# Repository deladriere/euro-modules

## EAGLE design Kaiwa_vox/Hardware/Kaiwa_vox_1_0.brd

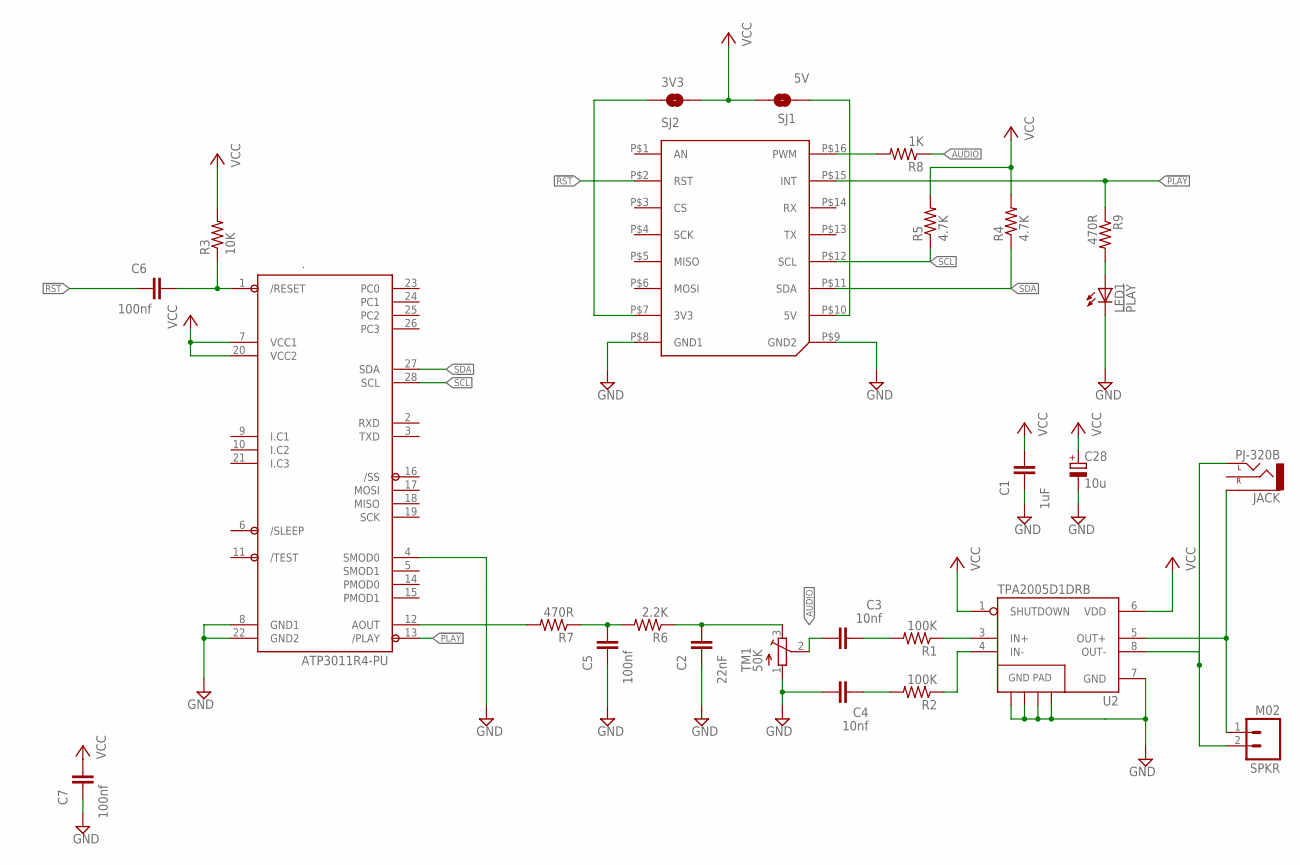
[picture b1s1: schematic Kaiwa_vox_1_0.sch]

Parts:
.: ATP3011R4-PU; DIP28
C1: 1uF; SPARKFUN_0805
C2: 22nF; SPARKFUN_0805
C3, C4: 10nf; SPARKFUN_0805
C5, C6, C7: 100nf; SPARKFUN_0805
C28: 10u; A/3216-18R
CLICK: MIKROE_CLICKLARGE; MIKROE_BUS_LARGE
JACK: PJ-320B; FOOTPRINT
LED1: !PLAY; SML0603
R1, R2: 100K; SPARKFUN_0805
R3: 10K; SPARKFUN_0805
R4, R5: 4.7K; SPARKFUN_0805
R6: 2.2K; SPARKFUN_0805
R7, R9: 470R; SPARKFUN_0805
R8: 1K; SPARKFUN_0805
SJ1: 5V; SPARKFUN_SJ_2S-TRACE
SJ2: 3V3; SPARKFUN_SJ_2S-NO
SPKR: M02; 1X02_LOCK_LONGPADS
TM1: 50K; TC33X
U2: TPA2005D1DRB; QFN-8_PAD

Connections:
!PLAY: ..13 (/PLAY), CLICK.P$15 (INT), R9.1
!RST: C6.2, CLICK.P$2 (RST)
AUDIO: C3.1, R8.1, TM1.2 (S)
GND: ..4 (SMOD0), ..8 (GND1), ..22 (GND2), C1.2, C2.2, C4.1, C5.2, C7.2, C28.-, CLICK.P$8 (GND1), CLICK.P$9 (GND2), LED1.C, TM1.1 (A), U2.7 (GND), U2.10 (GND), U2.11 (GND), U2.12 (GND), U2.13 (GND)
unnamed: ..1 (/RESET), C6.1, R3.1
unnamed: JACK.4 (SLEEVE), SPKR.1, U2.5 (OUT+)
unnamed: CLICK.P$7 (3V3), SJ2.1
unnamed: CLICK.P$10 (5V), SJ1.1
unnamed: C5.1, R6.2, R7.1
unnamed: C2.1, R6.1, TM1.3 (E)
unnamed: JACK.2 (LEFT), SPKR.2, U2.8 (OUT-)
unnamed: R1.1, U2.3 (IN+)
unnamed: R2.1, U2.4 (IN-)
unnamed: C4.2, R2.2
unnamed: CLICK.P$16 (PWM), R8.2
unnamed: C3.2, R1.2
unnamed: LED1.A, R9.2
unnamed: ..12 (AOUT), R7.2
SCL: ..28 (SCL), CLICK.P$12 (SCL), R5.1
SDA: ..27 (SDA), CLICK.P$11 (SDA), R4.1
VCC: ..7 (VCC1), ..20 (VCC2), C1.1, C7.1, C28.+, R3.2, R4.2, R5.2, SJ1.2, SJ2.2, U2.1 (SHUTDOWN), U2.6 (VDD)

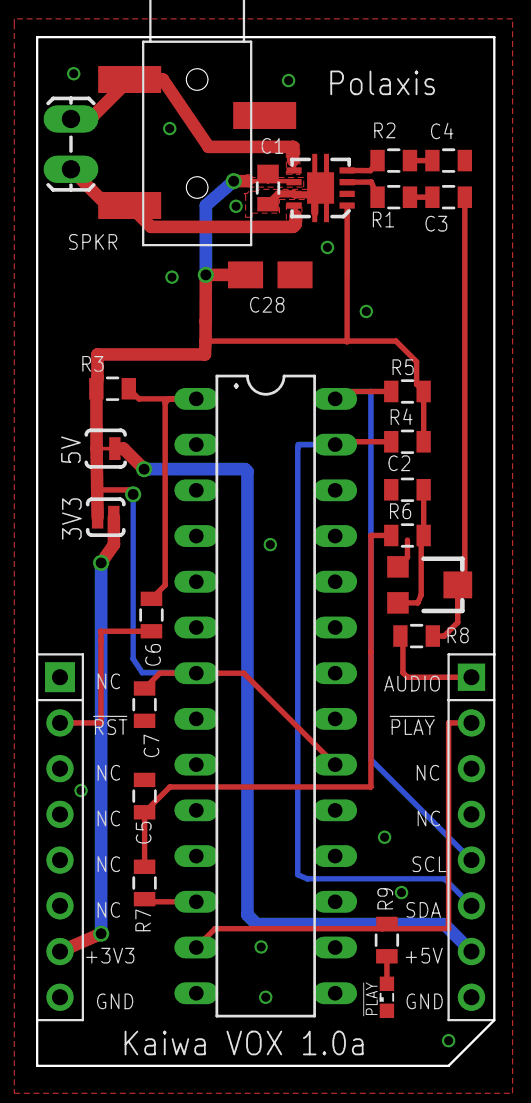
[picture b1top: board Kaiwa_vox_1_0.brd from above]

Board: 2 copper layers, 25.4 x 57.1 mm, 26 parts (0 on the bottom side), 21 nets.

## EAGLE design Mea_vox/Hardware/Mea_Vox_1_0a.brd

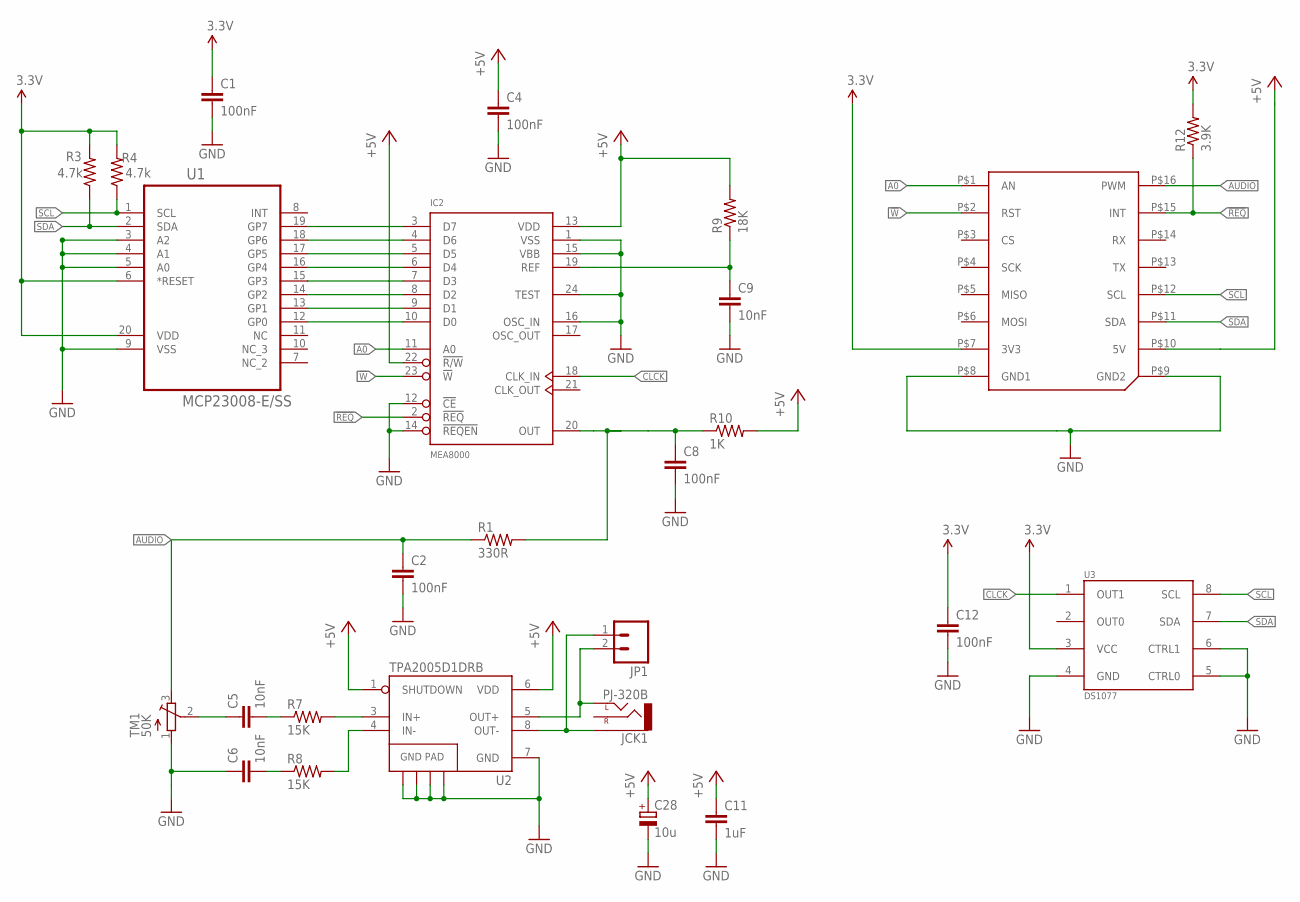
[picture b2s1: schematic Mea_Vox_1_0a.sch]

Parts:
C1, C2, C4, C8, C12: 100nF; SPARKFUN_0805
C5, C6, C9: 10nF; SPARKFUN_0805
C11: 1uF; SPARKFUN_0805
C28: 10u; A/3216-18R
IC2: MEA8000; DIL24-6
JCK1: PJ-320B; FOOTPRINT
JP1: M02PTH; 1X02
MK1: MIKROE_CLICKLARGE; MIKROE_BUS_LARGE
R1: 330R; SPARKFUN_0805
R3, R4: 4.7k; SPARKFUN_0805
R7, R8: 15K; SPARKFUN_0805
R9: 18K; SPARKFUN_0805
R10: 1K; SPARKFUN_0805
R12: 3.9K; SPARKFUN_0805
TM1: 50K; TC33X
U1: MCP23008-E/SS; SOP65P780X200-20N
U2: TPA2005D1DRB; QFN-8_PAD
U3: DS1077; SO08

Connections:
3.3V: C1.1, C12.1, MK1.P$7 (3V3), R3.2, R4.2, R12.2, U1.6 (*RESET), U1.20 (VDD), U3.3 (VCC)
!REQ: IC2.2 (!REQ), MK1.P$15 (INT), R12.1
!W: IC2.23 (!W), MK1.P$2 (RST)
+5V: C4.1, C11.1, C28.+, IC2.13 (VDD), IC2.22 (!R/W), MK1.P$10 (5V), R9.2, R10.2, U2.1 (SHUTDOWN), U2.6 (VDD)
A0: IC2.11 (A0), MK1.P$1 (AN)
AUDIO: C2.1, MK1.P$16 (PWM), R1.1, TM1.3 (E)
CLCK: IC2.18 (CLK_IN), U3.1 (OUT1)
GND: C1.2, C2.2, C4.2, C6.1, C8.2, C9.2, C11.2, C12.2, C28.-, IC2.1 (VSS), IC2.12 (!CE), IC2.14 (!REQEN), IC2.15 (VBB), IC2.16 (OSC_IN), IC2.24 (TEST), MK1.P$8 (GND1), MK1.P$9 (GND2), TM1.1 (A), U1.3 (A2), U1.4 (A1), U1.5 (A0), U1.9 (VSS), U2.7 (GND), U2.10 (GND), U2.11 (GND), U2.12 (GND), U2.13 (GND), U3.4 (GND), U3.5 (CTRL0), U3.6 (CTRL1)
unnamed: JCK1.4 (SLEEVE), JP1.1, U2.8 (OUT-)
unnamed: IC2.10 (D0), U1.12 (GP0)
unnamed: IC2.9 (D1), U1.13 (GP1)
unnamed: IC2.8 (D2), U1.14 (GP2)
unnamed: IC2.7 (D3), U1.15 (GP3)
unnamed: IC2.6 (D4), U1.16 (GP4)
unnamed: IC2.5 (D5), U1.17 (GP5)
unnamed: IC2.4 (D6), U1.18 (GP6)
unnamed: IC2.3 (D7), U1.19 (GP7)
unnamed: JCK1.2 (LEFT), JP1.2, U2.5 (OUT+)
unnamed: R7.2, U2.3 (IN+)
unnamed: R8.2, U2.4 (IN-)
unnamed: C6.2, R8.1
unnamed: C5.2, R7.1
unnamed: C8.1, IC2.20 (OUT), R1.2, R10.1
unnamed: C5.1, TM1.2 (S)
unnamed: C9.1, IC2.19 (REF), R9.1
SCL: MK1.P$12 (SCL), R4.1, U1.1 (SCL), U3.8 (SCL)
SDA: MK1.P$11 (SDA), R3.1, U1.2 (SDA), U3.7 (SDA)

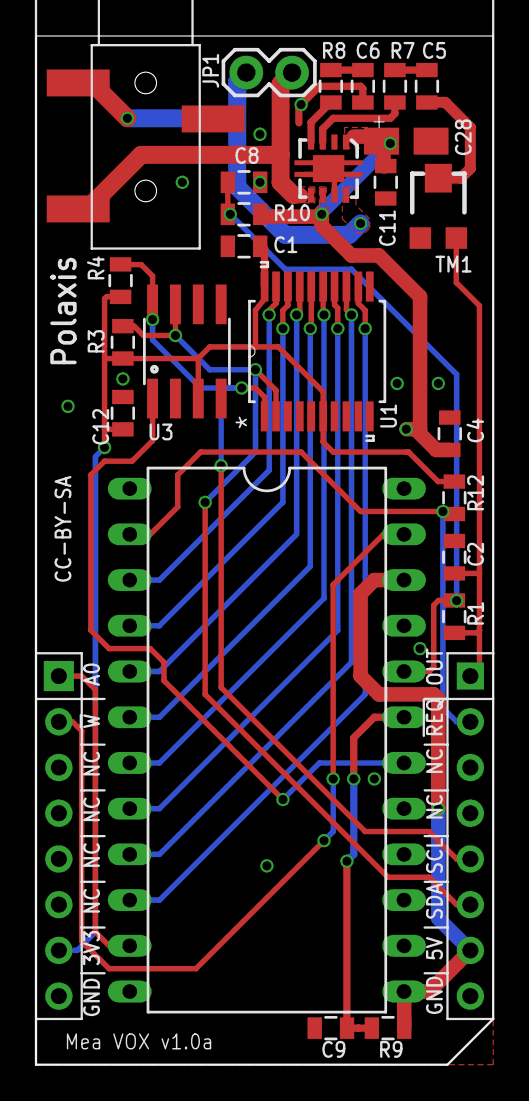
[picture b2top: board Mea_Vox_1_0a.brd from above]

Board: 2 copper layers, 25.4 x 57.1 mm, 26 parts (0 on the bottom side), 27 nets.

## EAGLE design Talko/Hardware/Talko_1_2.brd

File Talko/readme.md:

### Hardware revisions

Talko 1.0 (October 2014)
- initial release

Talko 1.1 (June 2015)
- higher resistors values for the LED (too bright) 
- removed the RC filter : I prefer the metallic sound it produces without the RC audio filter 
- swap Pitch & Speed pots as suggested
- fixed the LED ground connection missing

Talko 1.2 (May 2016)
- fixed a missing via
 - Audio output protected against mistake of over or under voltage by clipping from 0 to +5V 
- Rotary encoder for instant Bank change via interrupts
- Encoder's button to simulate gate signal going HIGH and make the module speak when pressed 
- Mode selection now a 3 positions switch 
- Break out 4 ATmega328p free pins for hacking (included A4 A5 for I2C bus) 
- Proper orientation of potentiomers

### Software revisions

Please note that hardware version need specific firmware version. They are not cross-compatible 

More info here : http://www.polaxis.be/talko/  
License: CC-BY-SA

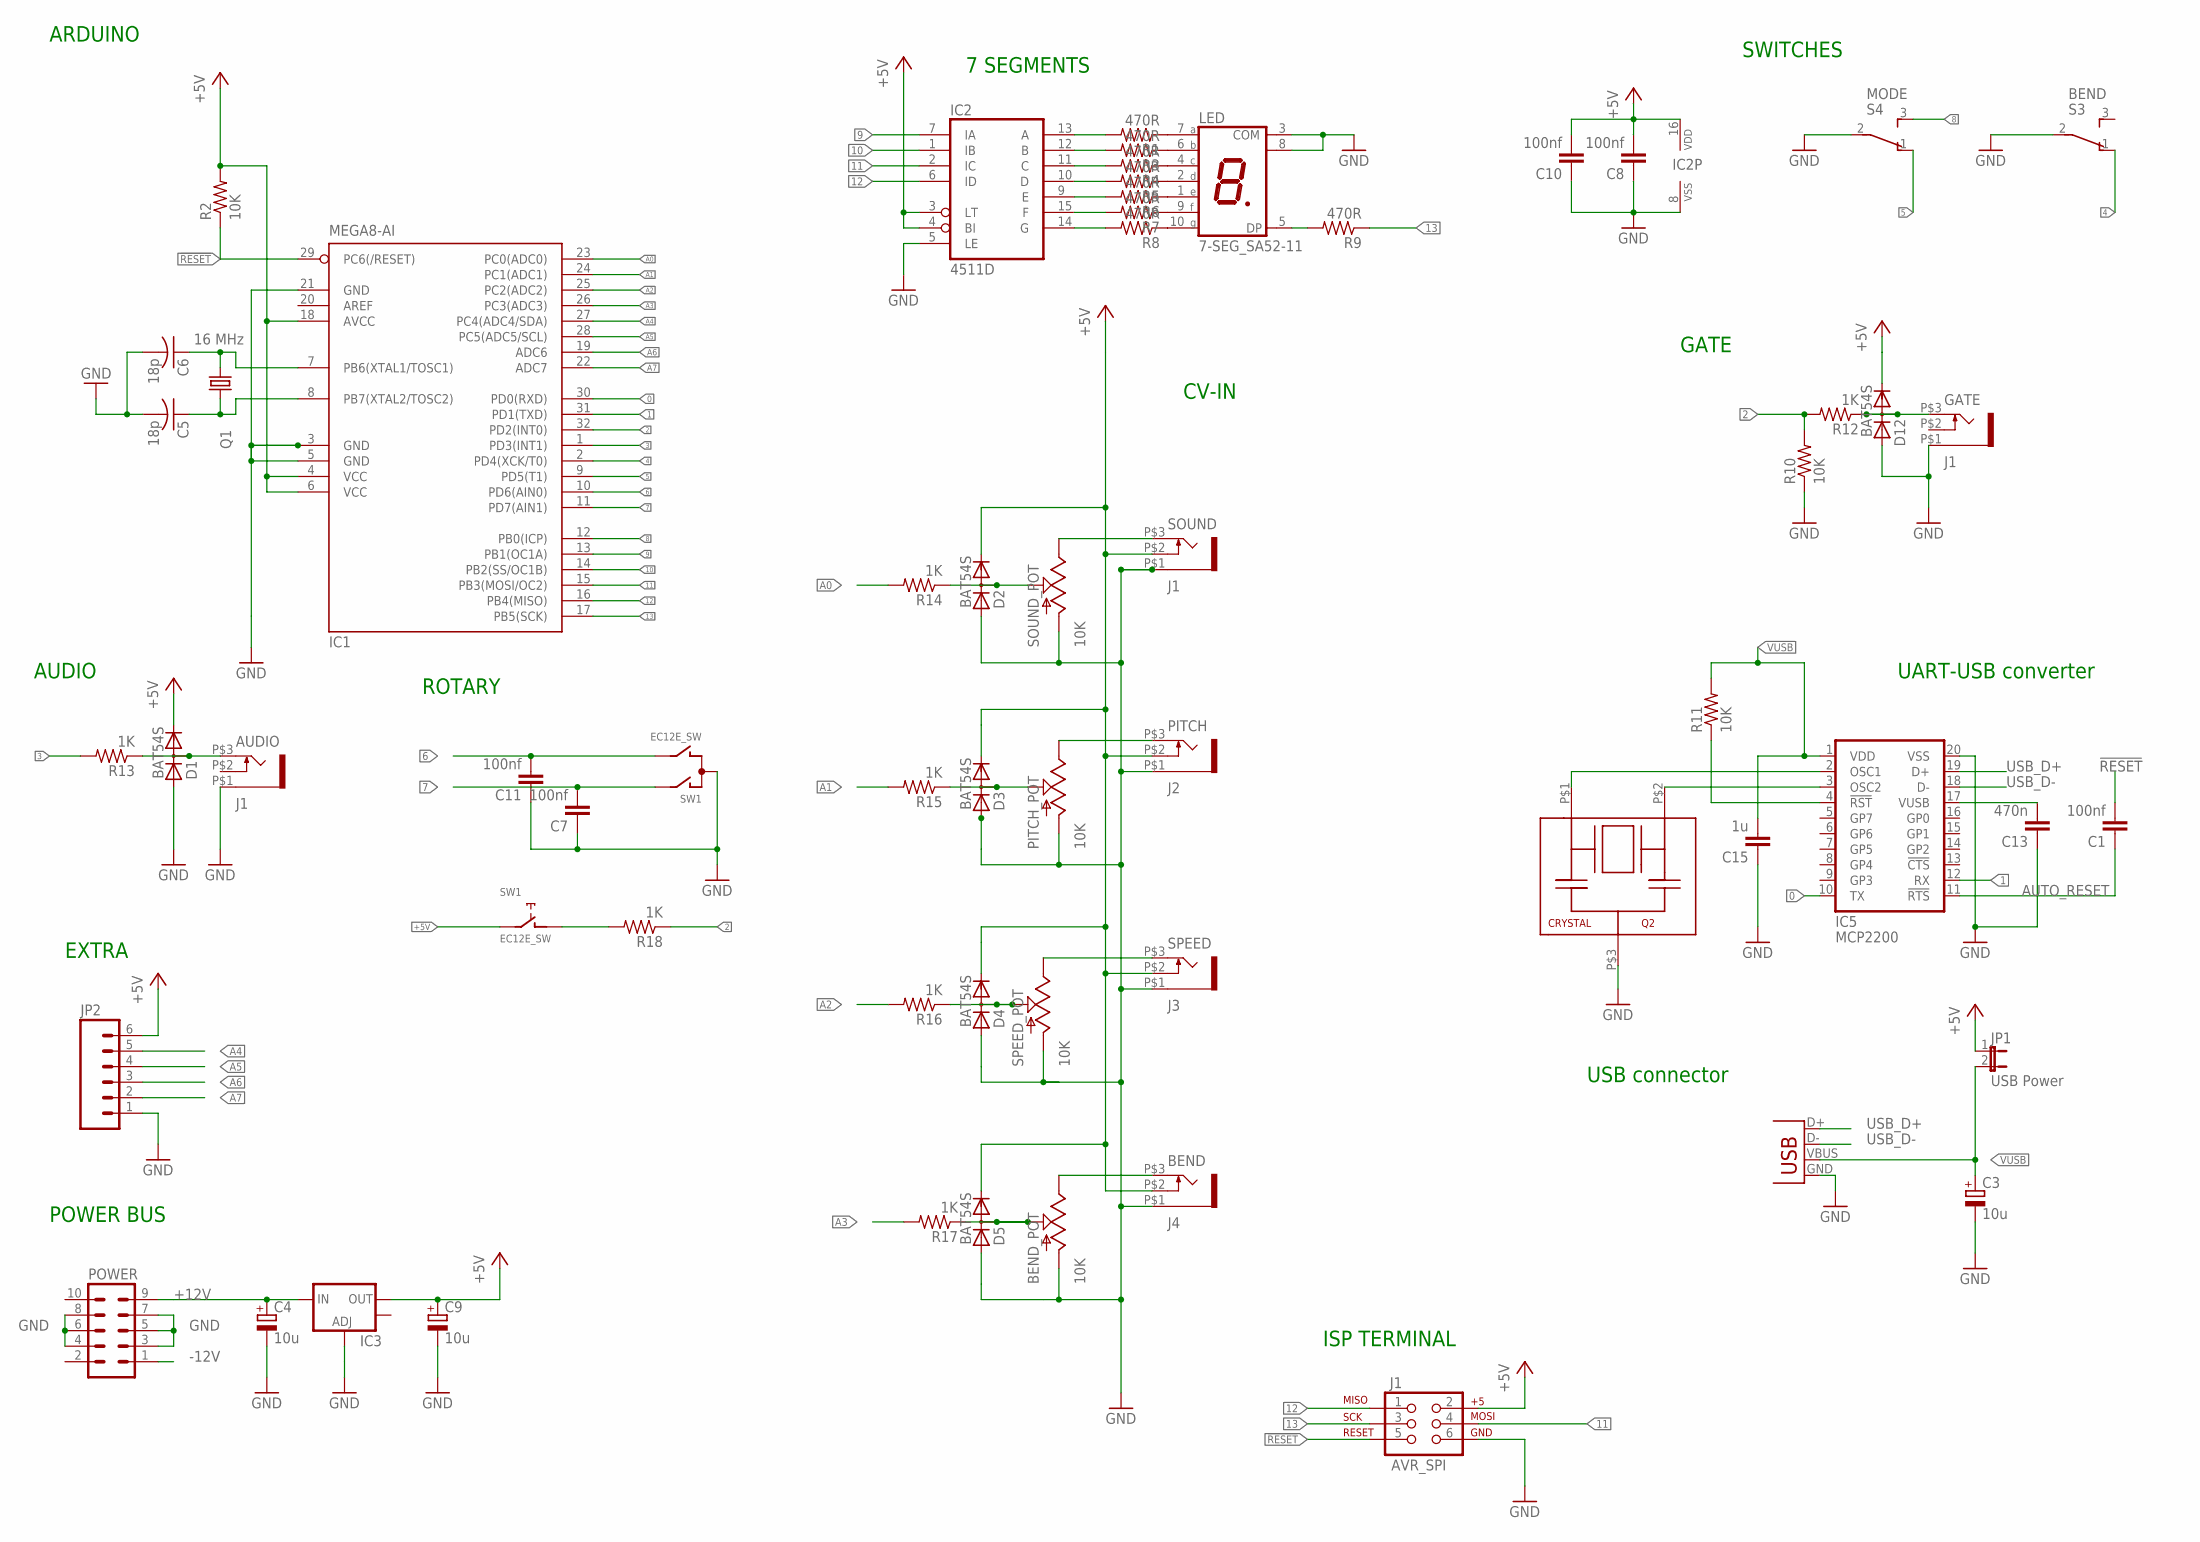
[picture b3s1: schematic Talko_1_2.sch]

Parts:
AUDIO: J1; THONKICONN
BEND: J4; THONKICONN
BEND_POT: 10K; ALPS_POT
C1, C7, C8, C10, C11: 100nf; C0805
C3, C4, C9: 10u; R/2012-12R
C5, C6: 18p; C0805K
C13: 470n; 0805
C15: 1u; 0805
D1, D2, D3, D4, D5, D12: BAT54S; SOT23
GATE: J1; THONKICONN
IC1: MEGA8-AI; TQFP32-08
IC2: 4511D; SO16
IC3: V_REG_LM1117SOT223; SOT223
IC5: MCP2200; SO20
J1: AVR_SPI; 2X3_LOCK
JP1: USB Power; JP1
JP2: M06SIP; 1X06
LED: 7-SEG_SA52-11; SA52-11
PITCH: J2; THONKICONN
PITCH_POT: 10K; ALPS_POT
POWER: 10_PIN_HEADER; MA05-2
Q1: 16 MHz; CTS406
Q2: CRYSTAL
R1, R3, R4, R5, R6, R7, R8, R9: 470R; M0805
R2, R10, R11: 10K; M0805
R12, R13, R14, R15, R16, R17, R18: 1K; M0805
S3: BEND; TL3XPO
S4: MODE; TL3XPO
SOUND: J1; THONKICONN
SOUND_POT: 10K; ALPS_POT
SPEED: J3; THONKICONN
SPEED_POT: 10K; ALPS_POT
SW1: EC12E_SW; ALPS_EC12E_SW
X3: USB; USB-B-PTH-VERTICAL

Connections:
0: IC1.30 (PD0(RXD)), IC5.10 (TX)
1: IC1.31 (PD1(TXD)), IC5.12 (RX)
2: IC1.32 (PD2(INT0)), R10.2, R12.2, R18.1
3: IC1.1 (PD3(INT1)), R13.2
4: IC1.2 (PD4(XCK/T0)), S3.1 (O)
5: IC1.9 (PD5(T1)), S4.1 (O)
6: C11.2, IC1.10 (PD6(AIN0)), SW1.B
7: C7.2, IC1.11 (PD7(AIN1)), SW1.A
8: IC1.12 (PB0(ICP)), S4.3 (S)
9: IC1.13 (PB1(OC1A)), IC2.7 (IA)
10: IC1.14 (PB2(SS/OC1B)), IC2.1 (IB)
11: IC1.15 (PB3(MOSI/OC2)), IC2.2 (IC), J1.4
12: IC1.16 (PB4(MISO)), IC2.6 (ID), J1.1
13: IC1.17 (PB5(SCK)), J1.3, R9.1
!RESET: C1.2, IC1.29 (PC6(/RESET)), J1.5, R2.1
+5V: BEND.P$2 (4), C8.2, C9.+, C10.2, D1.2 (C), D2.2 (C), D3.2 (C), D4.2 (C), D5.2 (C), D12.2 (C), IC1.4 (VCC), IC1.6 (VCC), IC1.18 (AVCC), IC2.3 (LT), IC2.4 (BI), IC2.16 (VDD), IC3.2 (OUT), J1.2, JP1.1, JP2.6, PITCH.P$2 (4), R2.2, SOUND.P$2 (4), SPEED.P$2 (4), SW1.E (2)
+12V: C4.+, IC3.3 (IN), POWER.9
-12V: POWER.1
A0: IC1.23 (PC0(ADC0)), R14.2
A1: IC1.24 (PC1(ADC1)), R15.2
A2: IC1.25 (PC2(ADC2)), R16.2
A3: IC1.26 (PC3(ADC3)), R17.2
A4: IC1.27 (PC4(ADC4/SDA)), JP2.5
A5: IC1.28 (PC5(ADC5/SCL)), JP2.4
A6: IC1.19 (ADC6), JP2.3
A7: IC1.22 (ADC7), JP2.2
AUTO_RESET: C1.1, IC5.11 (!RTS)
GND: AUDIO.P$1 (5), BEND.P$1 (5), BEND_POT.P$3 (A), C3.-, C4.-, C5.2, C6.2, C7.1, C8.1, C9.-, C10.1, C11.1, C13.1, C15.1, D1.1 (A), D2.1 (A), D3.1 (A), D4.1 (A), D5.1 (A), D12.1 (A), GATE.P$1 (5), IC1.3 (GND), IC1.5 (GND), IC1.21 (GND), IC2.5 (LE), IC2.8 (VSS), IC3.1 (ADJ), IC5.20 (VSS), J1.6, JP2.1, LED.3 (COM), LED.8 (COM), PITCH.P$1 (5), PITCH_POT.P$3 (A), POWER.3, POWER.4, POWER.5, POWER.6, POWER.7, POWER.8, Q2.P$3 (3), R10.1, S3.2, S4.2, SOUND.P$1 (5), SOUND_POT.P$3 (A), SPEED.P$1 (5), SPEED_POT.P$3 (A), SW1.C, X3.GND
unnamed: D12.3 (AC), GATE.P$3 (3), R12.1
unnamed: SOUND.P$3 (3), SOUND_POT.P$1 (E)
unnamed: C5.1, IC1.8 (PB7(XTAL2/TOSC2)), Q1.1
unnamed: LED.5 (DP), R9.2
unnamed: PITCH.P$3 (3), PITCH_POT.P$1 (E)
unnamed: AUDIO.P$3 (3), D1.3 (AC), R13.1
unnamed: SPEED.P$3 (3), SPEED_POT.P$1 (E)
unnamed: IC2.13 (A), R1.2
unnamed: D2.3 (AC), R14.1, SOUND_POT.P$2 (S)
unnamed: LED.7 (A), R1.1
unnamed: IC5.3 (OSC2), Q2.P$2 (2)
unnamed: C6.1, IC1.7 (PB6(XTAL1/TOSC1)), Q1.3 (2)
unnamed: R18.2, SW1.D (1)
unnamed: IC2.12 (B), R3.2
unnamed: LED.6 (B), R3.1
unnamed: IC2.11 (C), R4.2
unnamed: LED.4 (C), R4.1
unnamed: IC2.10 (D), R5.2
unnamed: LED.2 (D), R5.1
unnamed: IC2.9 (E), R6.2
unnamed: LED.1 (E), R6.1
unnamed: IC2.15 (F), R7.2
unnamed: LED.9 (F), R7.1
unnamed: IC2.14 (G), R8.2
unnamed: LED.10 (G), R8.1
unnamed: IC5.2 (OSC1), Q2.P$1 (1)
unnamed: IC5.4 (!RST), R11.1
unnamed: C13.2, IC5.17 (VUSB)
unnamed: D4.3 (AC), R16.1, SPEED_POT.P$2 (S)
unnamed: D3.3 (AC), PITCH_POT.P$2 (S), R15.1
unnamed: BEND_POT.P$2 (S), D5.3 (AC), R17.1
unnamed: BEND.P$3 (3), BEND_POT.P$1 (E)
USB_D+: IC5.19 (D+), X3.D+
USB_D-: IC5.18 (D-), X3.D-
VUSB: C3.+, C15.2, IC5.1 (VDD), JP1.2, R11.2, X3.VBUS

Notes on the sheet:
7 SEGMENTS
UART-USB converter
USB connector
ISP TERMINAL
POWER BUS
ARDUINO
SWITCHES
GATE
CV-IN
ROTARY
EXTRA
AUDIO

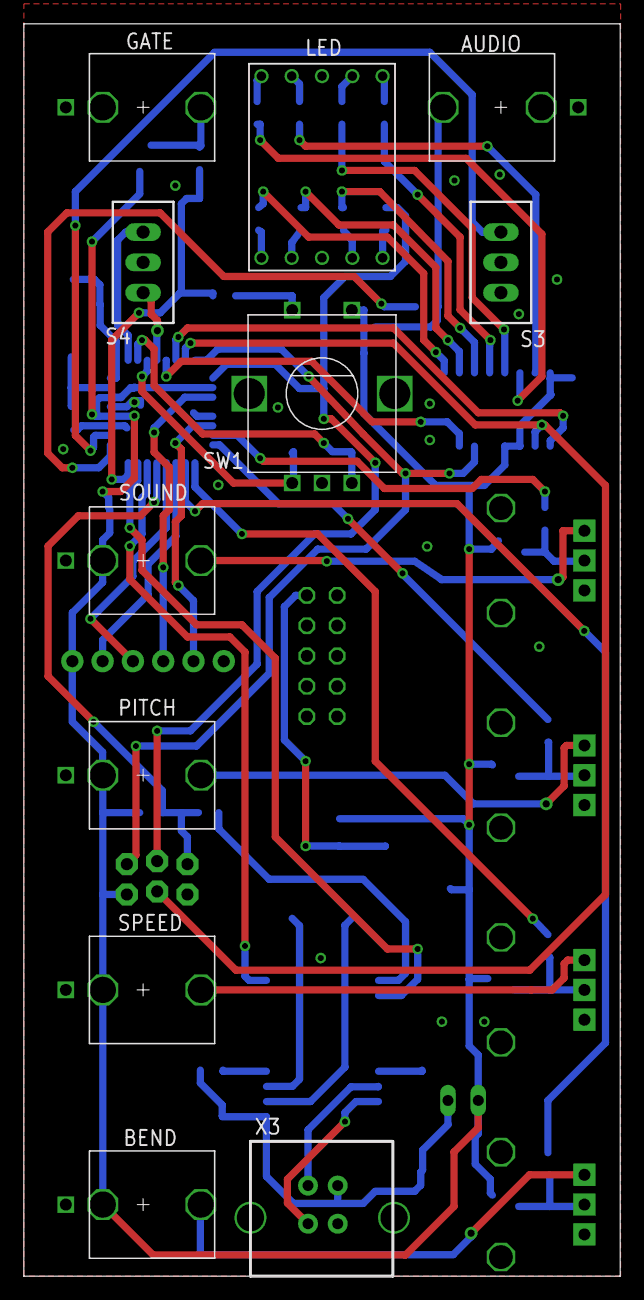
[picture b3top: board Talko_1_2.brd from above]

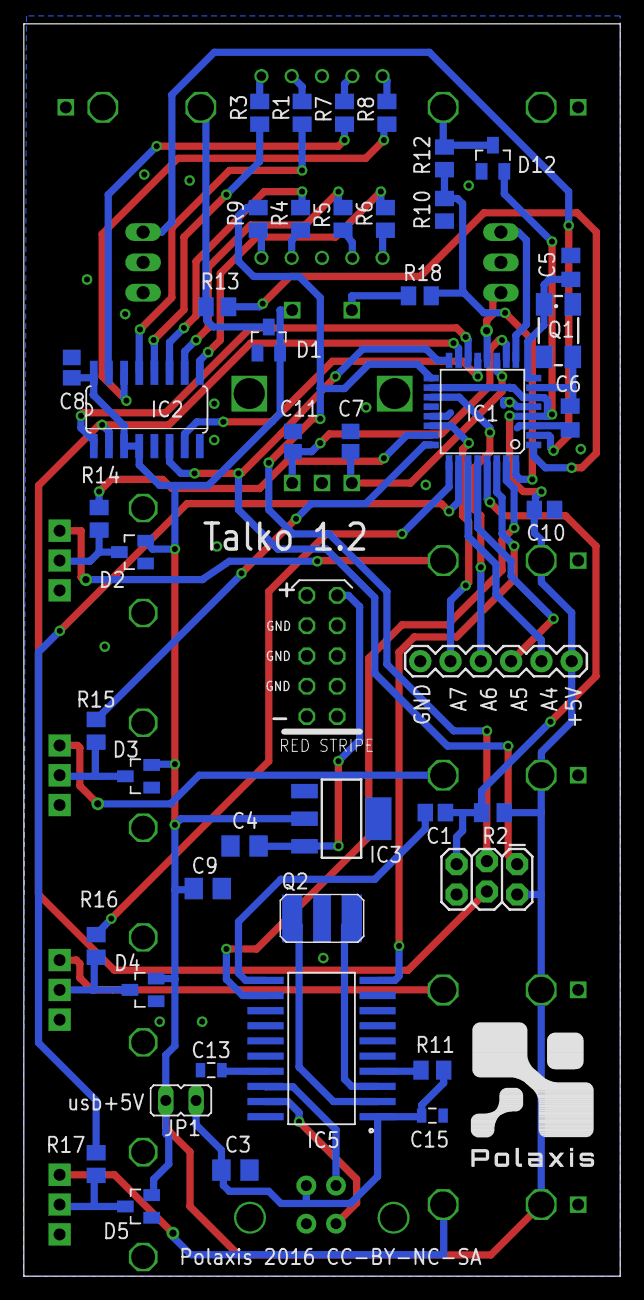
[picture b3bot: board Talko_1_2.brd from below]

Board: 2 copper layers, 50.0 x 105.0 mm, 61 parts (50 on the bottom side), 62 nets.

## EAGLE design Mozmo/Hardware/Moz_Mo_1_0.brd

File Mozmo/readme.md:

MozMo : the brilliant arduino Mozzi synth in an eurorack hardware.  

**Use Mozmo as bricks to build a complete modular synth**

[Mozzi library](http://sensorium.github.io/Mozzi/) by Tim Barras

Original hardware developer: Jean-Luc Deladriere 

**Please use hardware version 1.0 for now.** (1.1 is under construction)  

# Features :
- Arduino compatible with Usb connection
- Powered via Doepfer 5v bus or via Usb (via jumper)
- Uses Mozzi Hifi mode 
- 2 potentiometers 
- 2 CV entries 
- 1 gate entry 
- 1 audio out
- Depth : 40 mm
- Size : 6 hp

Hanabi 2006-2015. Except where otherwise noted, content on this site is licensed under a cc-by-sa 3.0 license.  

# Install [see this page](https://github.com/deladriere/euro-modules/wiki/install-mozmo) 

# Todo
- [ ] review bus power connector (from 16 pins to 10 pins)
- [ ] add 5V regulated power 78L05
- [ ] move C4 closer to ATmega328
- [ ] swap A1 & A0 on panel
- [ ] change 470 nF cap to 5.08 package (cheaper)
- [ ] add a DAC ? [see](https://github.com/jbeuckm/atmega_midi_cv_polysynth)

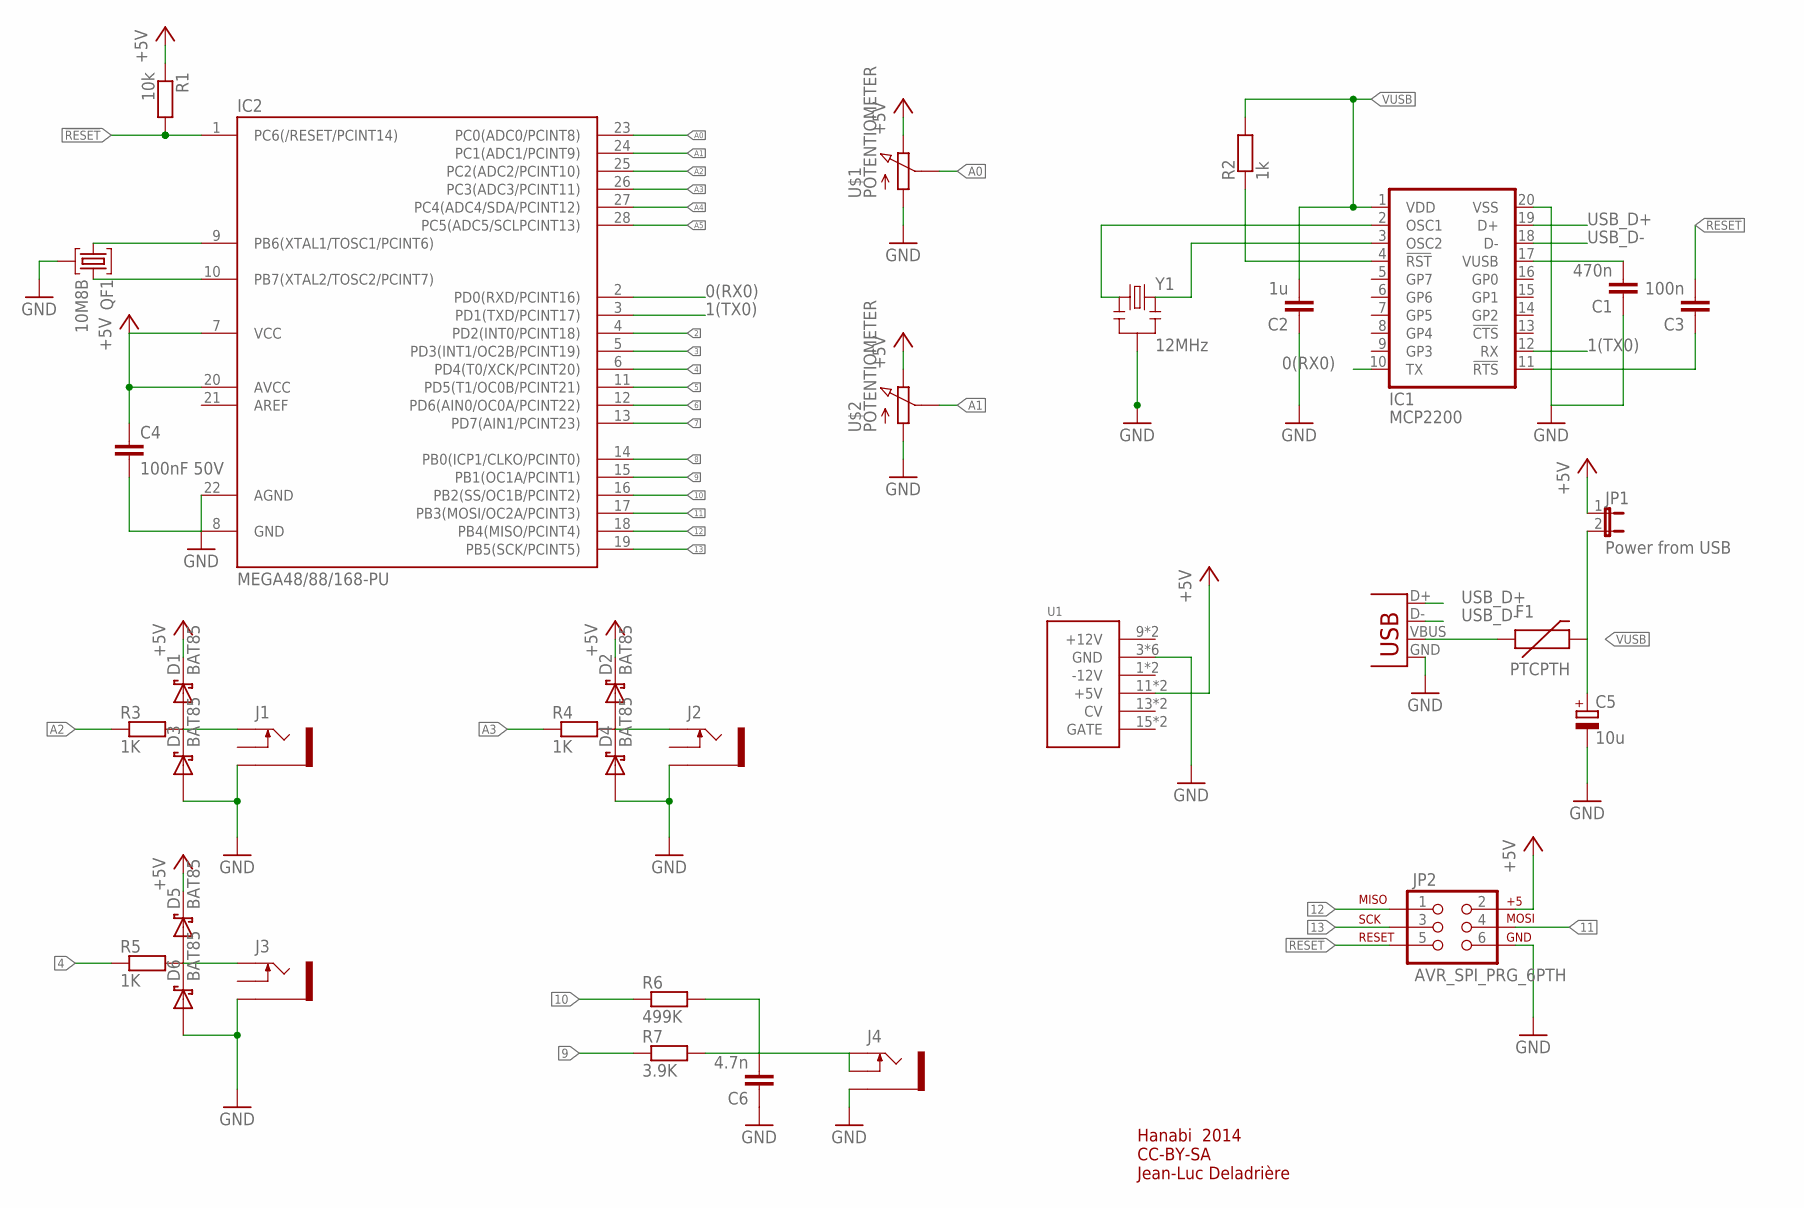
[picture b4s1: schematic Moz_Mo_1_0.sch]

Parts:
C1: 470n; CAP-PTH-SMALL
C2: 1u; CAP-PTH-5MM
C3: 100n; CAP-PTH-SMALL
C4: 100nF 50V; C025-025X050
C5: 10u; E2,5-7
C6: 4.7n; CAP-PTH-SMALL
D1, D2, D3, D4, D5, D6: BAT85; DIODE-TH-0.4
F1: PTCPTH; PTC
IC1: MCP2200; SO20
IC2: MEGA48/88/168-PU; DIL28-3
J1, J2, J3, J4: 1503_12
JP1: Power from USB; JP1
JP2: AVR_SPI_PRG_6PTH; 2X3
QF1: 10M8B; HC49U
R1: 10k; RES-AXIAL-0.4
R2: 1k; RES-AXIAL-0.4
R3, R4, R5: 1K; RES-AXIAL-0.4
R6: 499K; RES-AXIAL-0.4
R7: 3.9K; RES-AXIAL-0.4
U1: POWER; POWER_16
U$1, U$2: POTENTIOMETER
X1: USB; USB-B-PTH
Y1: 12MHz; HC49U-V-RESONATOR

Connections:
0(RX0): IC1.10 (TX), IC2.2 (PD0(RXD/PCINT16))
1(TX0): IC1.12 (RX), IC2.3 (PD1(TXD/PCINT17))
2: IC2.4 (PD2(INT0/PCINT18))
3: IC2.5 (PD3(INT1/OC2B/PCINT19))
4: IC2.6 (PD4(T0/XCK/PCINT20)), R5.P$1 (1)
5: IC2.11 (PD5(T1/OC0B/PCINT21))
6: IC2.12 (PD6(AIN0/OC0A/PCINT22))
7: IC2.13 (PD7(AIN1/PCINT23))
8: IC2.14 (PB0(ICP1/CLKO/PCINT0))
9: IC2.15 (PB1(OC1A/PCINT1)), R7.P$1 (1)
10: IC2.16 (PB2(SS/OC1B/PCINT2)), R6.P$1 (1)
11: IC2.17 (PB3(MOSI/OC2A/PCINT3)), JP2.4
12: IC2.18 (PB4(MISO/PCINT4)), JP2.1
13: IC2.19 (PB5(SCK/PCINT5)), JP2.3
!RESET: C3.2, IC2.1 (PC6(/RESET/PCINT14)), JP2.5, R1.P$2 (2)
+5V: C4.1, D1.C, D2.C, D5.C, IC2.7 (VCC), IC2.20 (AVCC), JP1.1, JP2.2, R1.P$1 (1), U1.11 (+5V), U1.12 (+5V), U$1.P$1 (E), U$2.P$1 (E)
A0: IC2.23 (PC0(ADC0/PCINT8)), U$1.P$2 (S)
A1: IC2.24 (PC1(ADC1/PCINT9)), U$2.P$2 (S)
A2: IC2.25 (PC2(ADC2/PCINT10)), R3.P$1 (1)
A3: IC2.26 (PC3(ADC3/PCINT11)), R4.P$1 (1)
A4: IC2.27 (PC4(ADC4/SDA/PCINT12))
A5: IC2.28 (PC5(ADC5/SCLPCINT13))
AUTO_RESET: C3.1, IC1.11 (!RTS)
GND: C1.1, C2.1, C4.2, C5.-, C6.1, D3.A, D4.A, D6.A, IC1.20 (VSS), IC2.8 (GND), IC2.22 (AGND), J1.5 (1), J2.5 (1), J3.5 (1), J4.5 (1), JP2.6, QF1.2, U1.3 (GND), U1.4 (GND), U1.5 (GND), U1.6 (GND), U1.7 (GND), U1.8 (GND), U$1.P$3 (A), U$2.P$3 (A), X1.GND, Y1.GND (2)
unnamed: F1.P$1 (1), X1.VBUS
unnamed: D1.A, D3.C, J1.3 (2), R3.P$2 (2)
unnamed: IC2.9 (PB6(XTAL1/TOSC1/PCINT6)), QF1.1
unnamed: D2.A, D4.C, J2.3 (2), R4.P$2 (2)
unnamed: D5.A, D6.C, J3.3 (2), R5.P$2 (2)
unnamed: C6.2, J4.3 (2), J4.4 (3), R6.P$2 (2), R7.P$2 (2)
unnamed: IC1.3 (OSC2), Y1.2 (3)
unnamed: IC2.10 (PB7(XTAL2/TOSC2/PCINT7)), QF1.3
unnamed: C1.2, IC1.17 (VUSB)
unnamed: IC1.2 (OSC1), Y1.1
unnamed: IC1.4 (!RST), R2.P$1 (1)
USB_D+: IC1.19 (D+), X1.D+
USB_D-: IC1.18 (D-), X1.D-
VUSB: C2.2, C5.+, F1.P$2 (2), IC1.1 (VDD), JP1.2, R2.P$2 (2)

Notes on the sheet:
Hanabi 2014 CC-BY-SA Jean-Luc Deladrière

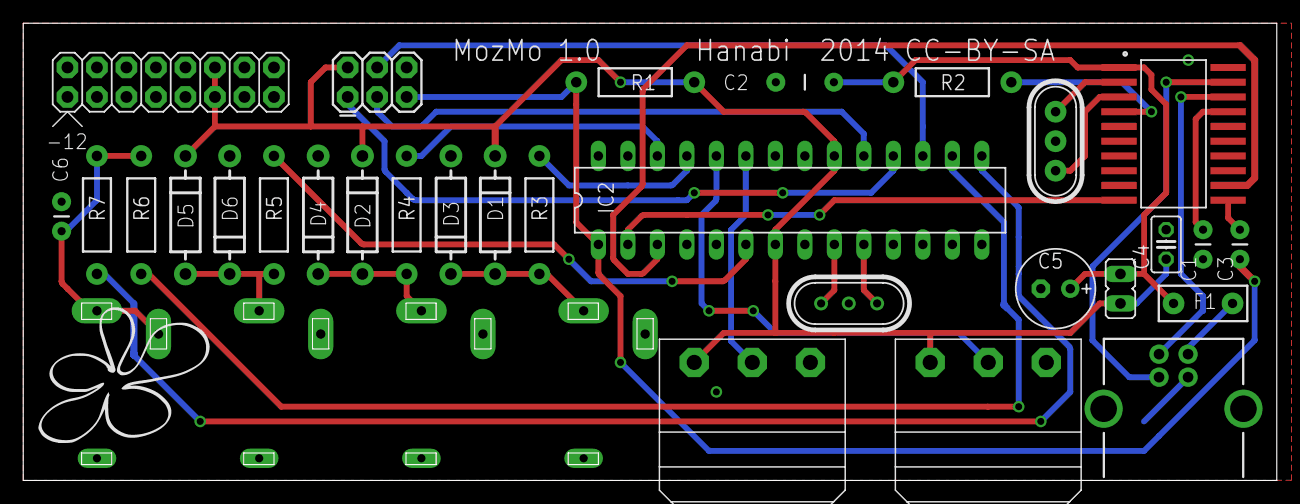
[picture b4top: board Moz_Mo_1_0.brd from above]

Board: 2 copper layers, 107.9 x 39.3 mm, 35 parts (0 on the bottom side), 30 nets.

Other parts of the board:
U$3: LOGO_HANABI

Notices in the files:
Talko/Hardware/Talko_1_2.brd:
Polaxis 2016 CC-BY-NC-SA
parts and their libraries:
DECADE-libraries: Licensing: CC v3.0 Share-Alike You are welcome to use this library for commercial purposes.
SparkFun-Connectors: Licensing: Creative Commons ShareAlike 4.0 International - https://creativecommons.org/licenses/by-sa/4.0
